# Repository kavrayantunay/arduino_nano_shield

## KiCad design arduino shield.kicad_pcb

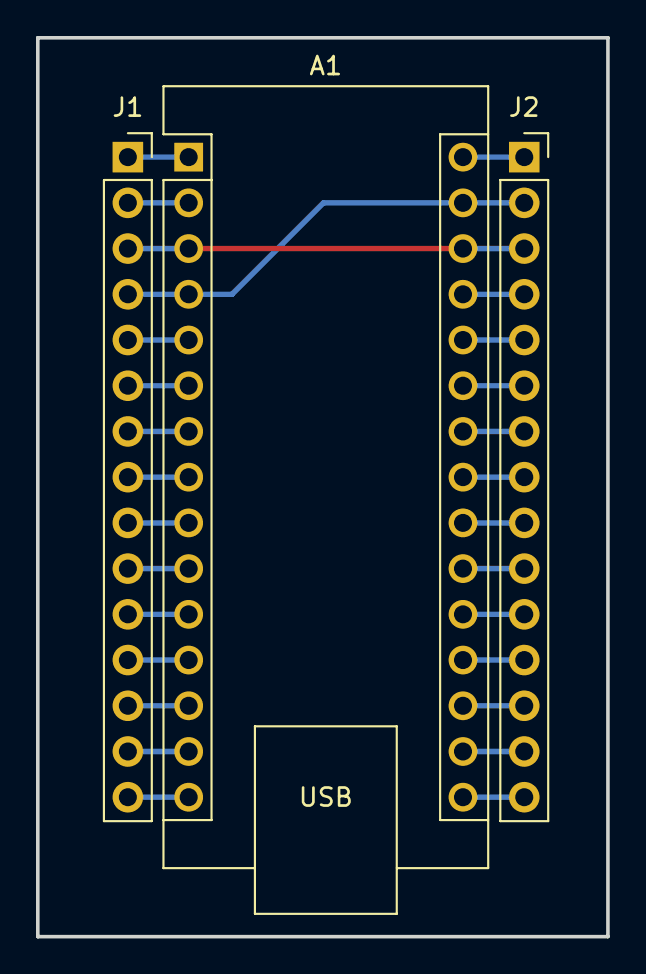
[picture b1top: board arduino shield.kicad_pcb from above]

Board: 2 copper layers, 31.7 x 49.9 mm, 3 parts (0 on the bottom side), 28 nets.

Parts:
A1: Arduino_Nano_v3.x; Arduino_Nano
J1, J2: Conn_01x15_Female; PinSocket_1x15_P2.54mm_Vertical

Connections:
+3.3V: A1.17 (3V3), J2.14
+5V: A1.27 (+5V), J2.4
A0: A1.19 (A0), J2.12
A1: A1.20 (A1), J2.11
A2: A1.21 (A2), J2.10
A3: A1.22 (A3), J2.9
A4: A1.23 (A4), J2.8
A5: A1.24 (A5), J2.7
A6: A1.25 (A6), J2.6
A7: A1.26 (A7), J2.5
AREF: A1.18 (AREF), J2.13
D2: A1.5 (D2), J1.5
D3: A1.6 (D3), J1.6
D4: A1.7 (D4), J1.7
D5: A1.8 (D5), J1.8
D6: A1.9 (D6), J1.9
D7: A1.10 (D7), J1.10
D8: A1.11 (D8), J1.11
D9: A1.12 (D9), J1.12
D10: A1.13 (D10), J1.13
D11: A1.14 (D11), J1.14
D12: A1.15 (D12), J1.15
D13: A1.16 (D13), J2.15
GND: A1.4 (GND), A1.29 (GND), J1.4, J2.2
RST: A1.3 (~RESET), A1.28 (~RESET), J1.3, J2.3
RX0: A1.2 (D0/RX), J1.2
TX1: A1.1 (D1/TX), J1.1
VIN: A1.30 (VIN), J2.1
